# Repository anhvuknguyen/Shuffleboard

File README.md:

# Shuffleboard

A two-player shuffleboard game for the TI MSPM0 LaunchPad, with a hand-written 2D physics engine, real-time audio playback, and a custom PCB for the input hardware.

Built as the final project for EE 319K (Introduction to Embedded Systems) at UT Austin.

**[▶ Demo video](https://youtu.be/GUb15umj7tY)**

---

## How it plays

Each player gets three pucks. You set your launch position with a slide potentiometer, aim with a joystick, and fire with a button. An on-screen arrow shows your aim in real time — its direction and length track the joystick, so the length doubles as a power indicator.

Once a puck is launched it slides, decelerates under friction, and collides with any pucks already on the board. When everything comes to rest, each puck is scored by the region its center is sitting on.

---

## Architecture

The system runs two interrupts at different rates, doing very different work.

### 30 Hz timer ISR (TIMG12) — simulation and rendering

Drives the game at 30 FPS. Each tick:

- Samples the joystick and slide pot from the external ADC over I²C
- Updates the aiming arrow's length and direction
- Integrates puck positions, applies friction, and resolves collisions
- Redraws the board

### 7 kHz SysTick ISR — audio

Streams PCM samples to the MSPM0's internal DAC one sample per tick. Sound effects were converted from WAV files into C arrays at build time, so playback is just walking an array and writing the DAC at a fixed rate.

### Why the two don't fight

The audio ISR fires roughly 233 times per physics frame, so anything slow inside the 30 Hz ISR risks starving it. The I²C reads are the slow part — a config write plus a conversion read on the ADS1115 is on the order of a millisecond.

That never becomes a problem, because the game's state machine keeps the two workloads disjoint:

| State | I²C sampling | Audio |
|---|---|---|
| Aiming | Yes | Idle |
| Puck motion / collision | No | Playing |
| Victory screen | No | Playing |

You can't aim while pucks are moving, and you can't shoot until every puck has come to rest. So the expensive input path and the expensive audio path are never live in the same frame.

---

## Physics

Pucks are modeled as circles with position, velocity, and a friction coefficient applied per frame. Collisions are detected by center-distance against the sum of the radii, and resolved elastically along the line connecting the two centers.

Scoring samples the board region underneath each puck's center once its velocity reaches zero, and adds the point value for that region's color.

---

## Hardware

Input devices live on a custom PCB designed in KiCad:

- **ADS1115** 16-bit external ADC, read over I²C — two single-ended channels for the joystick axis and the slide potentiometer
- **RC low-pass filters** on the fire and reset buttons for hardware debouncing, rather than handling bounce in software
- **Bulk decoupling capacitors** at the supply rails, to keep the rail from dipping below the MCU's minimum when the circuit draws current in bursts

---

## Building

Open the project in Code Composer Studio, select the MSPM0 LaunchPad target, and flash.

```
software/   game logic, physics, ISRs, PCM sample arrays generated from WAV files
hardware/   KiCad schematic and board files
```

---

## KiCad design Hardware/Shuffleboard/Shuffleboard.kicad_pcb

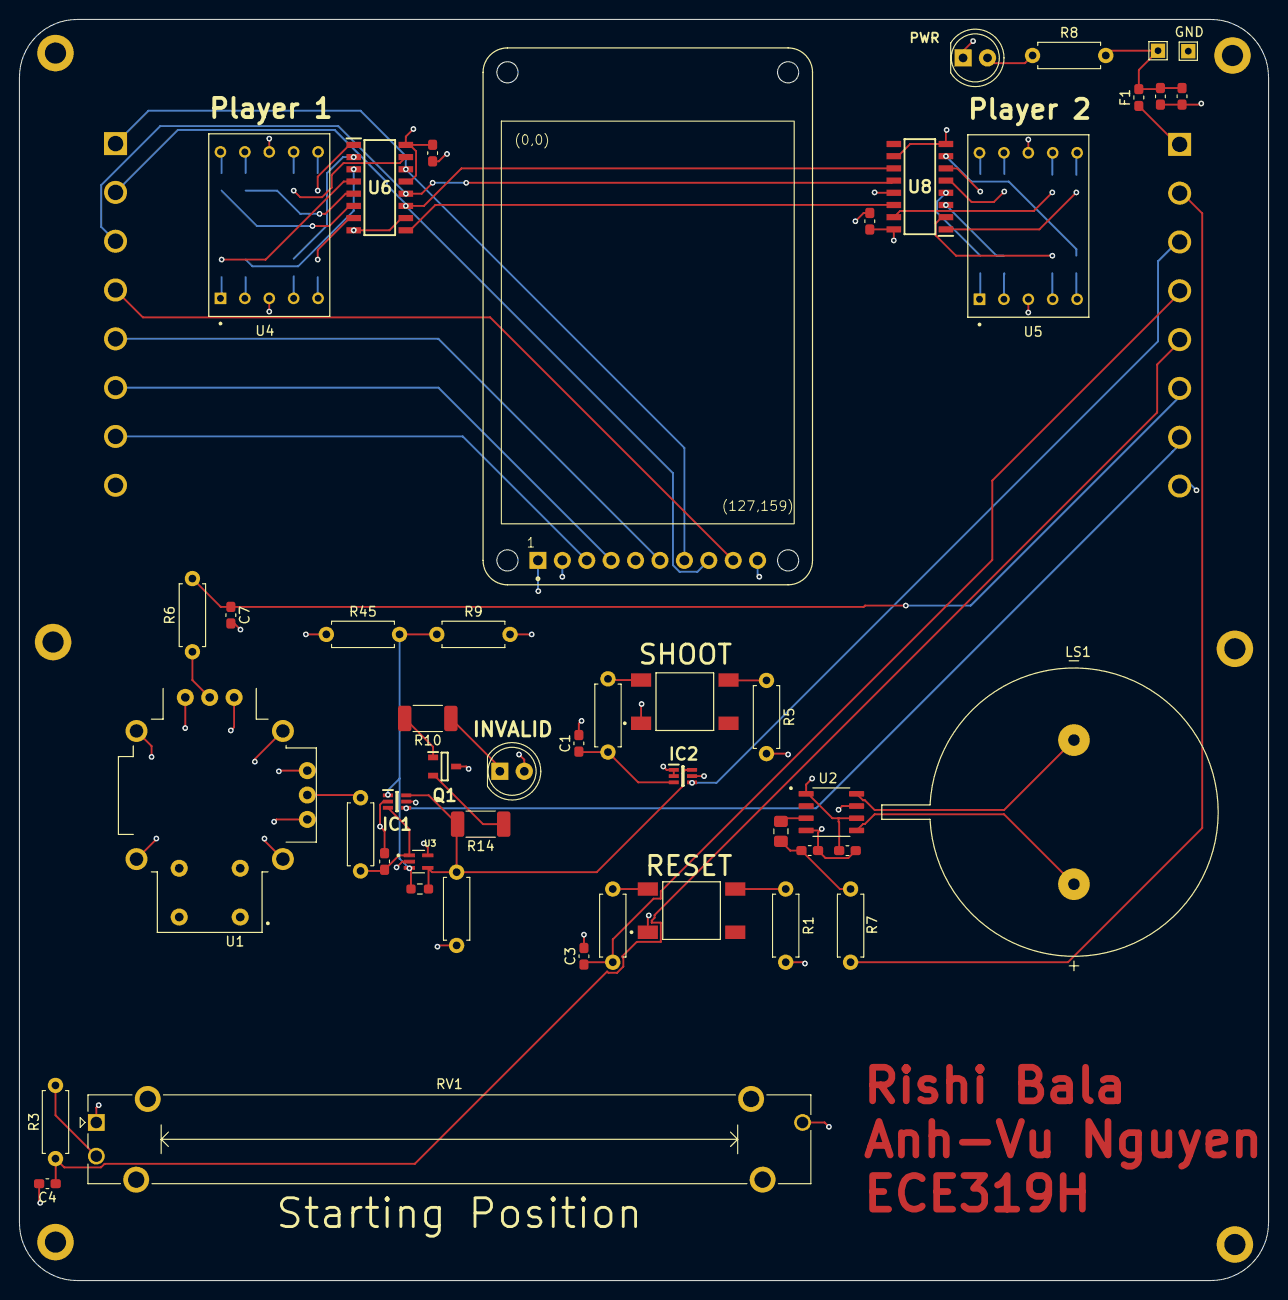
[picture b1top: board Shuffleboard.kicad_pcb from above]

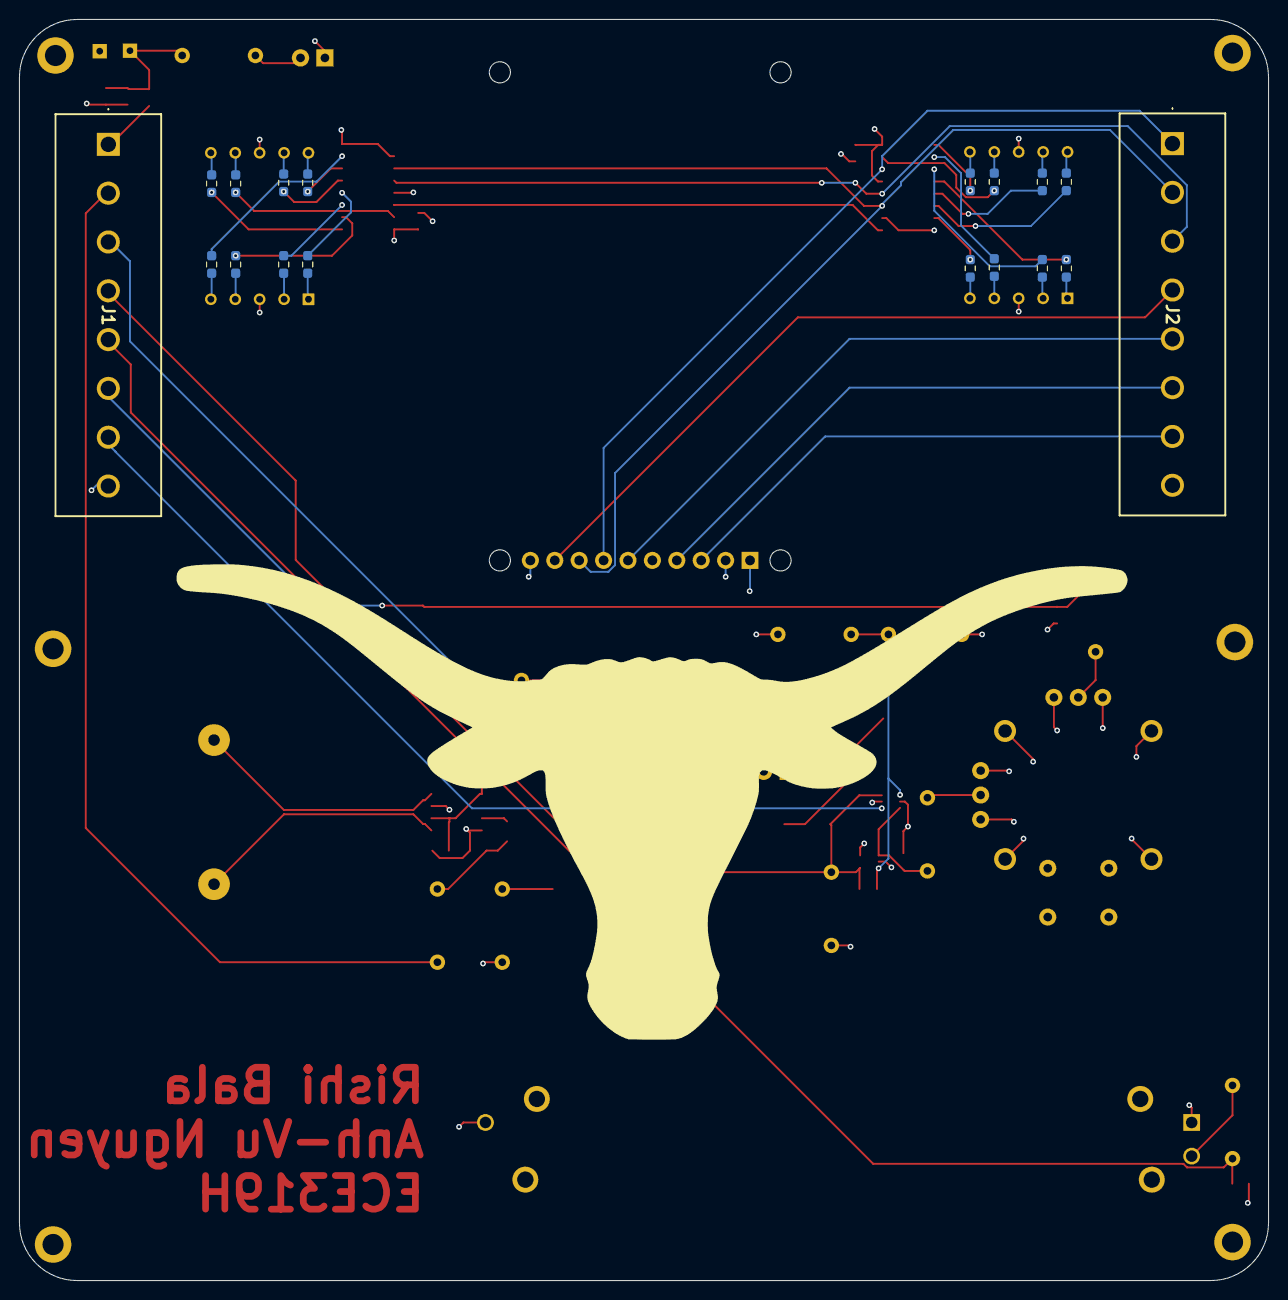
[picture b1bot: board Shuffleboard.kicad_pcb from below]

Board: 4 copper layers, 130.0 x 131.2 mm, 71 parts (18 on the bottom side), 68 nets.

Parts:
C1, C2, C3, C4, C5, C6, C7, C8, C10: C_0603_1608Metric_Pad1.08x0.95mm_HandSolder
C9: C_0805_2012Metric_Pad1.18x1.45mm_HandSolder
C11, C12: 100n; C_0603_1608Metric_Pad1.08x0.95mm_HandSolder
D1, D32: LED_D5.0mm
F1: Fuse_0603_1608Metric_Pad1.05x0.95mm_HandSolder
H1, H2, H3, H4, H5, H6: MountingHole_2.2mm_M2_DIN965_Pad
IC1, IC2: SOT65P210X110-6N
J1, J2: TBJ05-08-1-G-G; TBJ05081GG
LS1: SPKR_CMS-3012-18T
Q1: SOT95P260X110-3N
R1, R2, R3, R4, R5, R6, R7, R8, R9, R11, R12, R45: R_Axial_DIN0207_L6.3mm_D2.5mm_P7.62mm_Horizontal
R10, R14: R_2010_5025Metric_Pad1.40x2.65mm_HandSolder
R13, R15, R16, R17, R18, R19, R20, R21, R22, R23, R24, R25, R26, R27, R28, R29, R30: R_0603_1608Metric_Pad0.98x0.95mm_HandSolder
RV1: Potentiometer_Bourns_PTA6043_Single_Slide
S1, S2: SW_TL3301FF160QG
TP1, TP2: TestPoint_THTPad_1.5x1.5mm_Drill0.7mm
U1: XDCR_COM-09032
U2: SOIC127P600X170-8N
U3: lmv331
U4, U5: LED_INND-TS56RCB
U6, U8: SOIC127P600X175-16N
U7: adafruit_st7735r

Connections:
+3.3V: C2.1, C6.2, C10.2, C11.2, C12.1, D1.2 (A), F1.2, IC1.5 (V+), IC2.5 (V+), R8.2, R12.1, R45.1, RV1.1, S1.1, S2.1, TP2.1 (1_1), U1.H1 (H+), U1.V1 (V+), U2.1 (~SD), U2.6 (VDD), U3.5 (V+), U6.13 (G), U6.16 (VCC), U7.2 (VCC), U7.10 (LITE), U8.13 (G), U8.16 (VCC)
/3.3VIN: F1.1, J1.1
/7Seg/QH1: U6.9 (QH*), U8.14 (SER)
/Connector/HOR_PB18_ADC1_5: C7.1, J1.6, R6.2
/Connector/POS_PB17_ADC1_4: C4.1, J1.5, R3.2
/Connector/VER_PB19_ADC1_6: IC1.4 (A), J1.7
/DACOut: J1.2, R7.1
/Inputs/CompOut: IC1.6 (S), IC2.6 (S), R12.2, R13.2, R14.2, U3.4
/Inputs/SHOOT_SW: C1.1, IC2.3 (B0), R11.2
/Inputs/VER_POT: C5.1, IC1.3 (B0), R4.2, U3.1 (+)
/Inputs/Vref: IC1.1 (B1), R9.1, R13.1, R45.2, U3.3 (-)
/PA13_DC: J2.6, U7.4 (D/C)
/PB1RST: C3.1, J1.4, R2.2
/PB4SHOOT: IC2.4 (A), J1.3
/PB6_CS: J2.5, U7.6 (TFT_CS)
/PB7_MISO: J2.4, U7.9 (MISO)
/PB8_MOSI: J2.1, U6.14 (SER), U7.7 (MOSI)
/PB9_SPI_CLK: J2.2, U6.11 (SCK), U7.8 (SCK), U8.11 (SCK)
/PB15_RESET: J2.7, U7.3 (RESET)
/PB16_L/P: J2.3, U6.12 (RCK), U8.12 (RCK)
/Speaker/OUT+: LS1.P, U2.5 (OUT+)
/Speaker/OUT-: LS1.N, U2.8 (OUT-)
GND: C1.2, C2.2, C3.2, C4.2, C5.2, C6.1, C7.2, C8.2, C10.1, C11.1, C12.2, D32.1 (K), IC1.2 (GND), IC2.1 (B1), IC2.2 (GND), J1.8, J2.8, Q1.3 (S), R1.2, R5.2, R9.2, RV1.3, TP1.1 (1_1), U1.H3 (H-), U1.S1 (SHIELD), U1.S2 (SHIELD), U1.S3 (SHIELD), U1.S4 (SHIELD), U1.V3 (V-), U2.4 (IN-), U2.7 (GND), U3.2 (V-), U4.3, U4.8, U5.3, U5.8, U6.8 (GND), U6.10 (SCL), U7.1 (GND), U8.8 (GND), U8.10 (SCL)
unnamed: C8.1, C9.1, R7.2
unnamed: D1.1 (K), R10.1
unnamed: D32.2 (A), R8.1
unnamed: Q1.1 (D), R10.2
unnamed: Q1.2 (G), R14.1
unnamed: R1.1, S2.4
unnamed: R2.1, S2.3
unnamed: R3.1, RV1.2
unnamed: R5.1, S1.4
unnamed: R11.1, S1.3
unnamed: R15.2, U4.7
unnamed: R16.2, U4.6
unnamed: R17.2, U4.4
unnamed: R18.2, U4.2
unnamed: R19.2, U4.1
unnamed: R20.2, U4.9
unnamed: R21.2, U4.10
unnamed: R22.2, U4.5
unnamed: R23.2, U5.7
unnamed: R24.2, U5.6
unnamed: R25.2, U5.4
unnamed: R26.2, U5.2
unnamed: R27.2, U5.1
unnamed: R28.2, U5.9
unnamed: R29.2, U5.10
unnamed: R30.2, U5.5
unnamed: R6.1, U1.H2 (H)
unnamed: R4.1, U1.V2 (V)
unnamed: C9.2, U2.3 (IN+)
unnamed: R15.1, U6.15 (QA)
unnamed: R16.1, U6.1 (QB)
unnamed: R17.1, U6.2 (QC)
unnamed: R18.1, U6.3 (QD)
unnamed: R19.1, U6.4 (QE)
unnamed: R20.1, U6.5 (QF)
unnamed: R21.1, U6.6 (QG)
unnamed: R22.1, U6.7 (QH)
unnamed: R23.1, U8.15 (QA)
unnamed: R24.1, U8.1 (QB)
unnamed: R25.1, U8.2 (QC)
unnamed: R26.1, U8.3 (QD)
unnamed: R27.1, U8.4 (QE)
unnamed: R28.1, U8.5 (QF)
unnamed: R29.1, U8.6 (QG)
unnamed: R30.1, U8.7 (QH)
